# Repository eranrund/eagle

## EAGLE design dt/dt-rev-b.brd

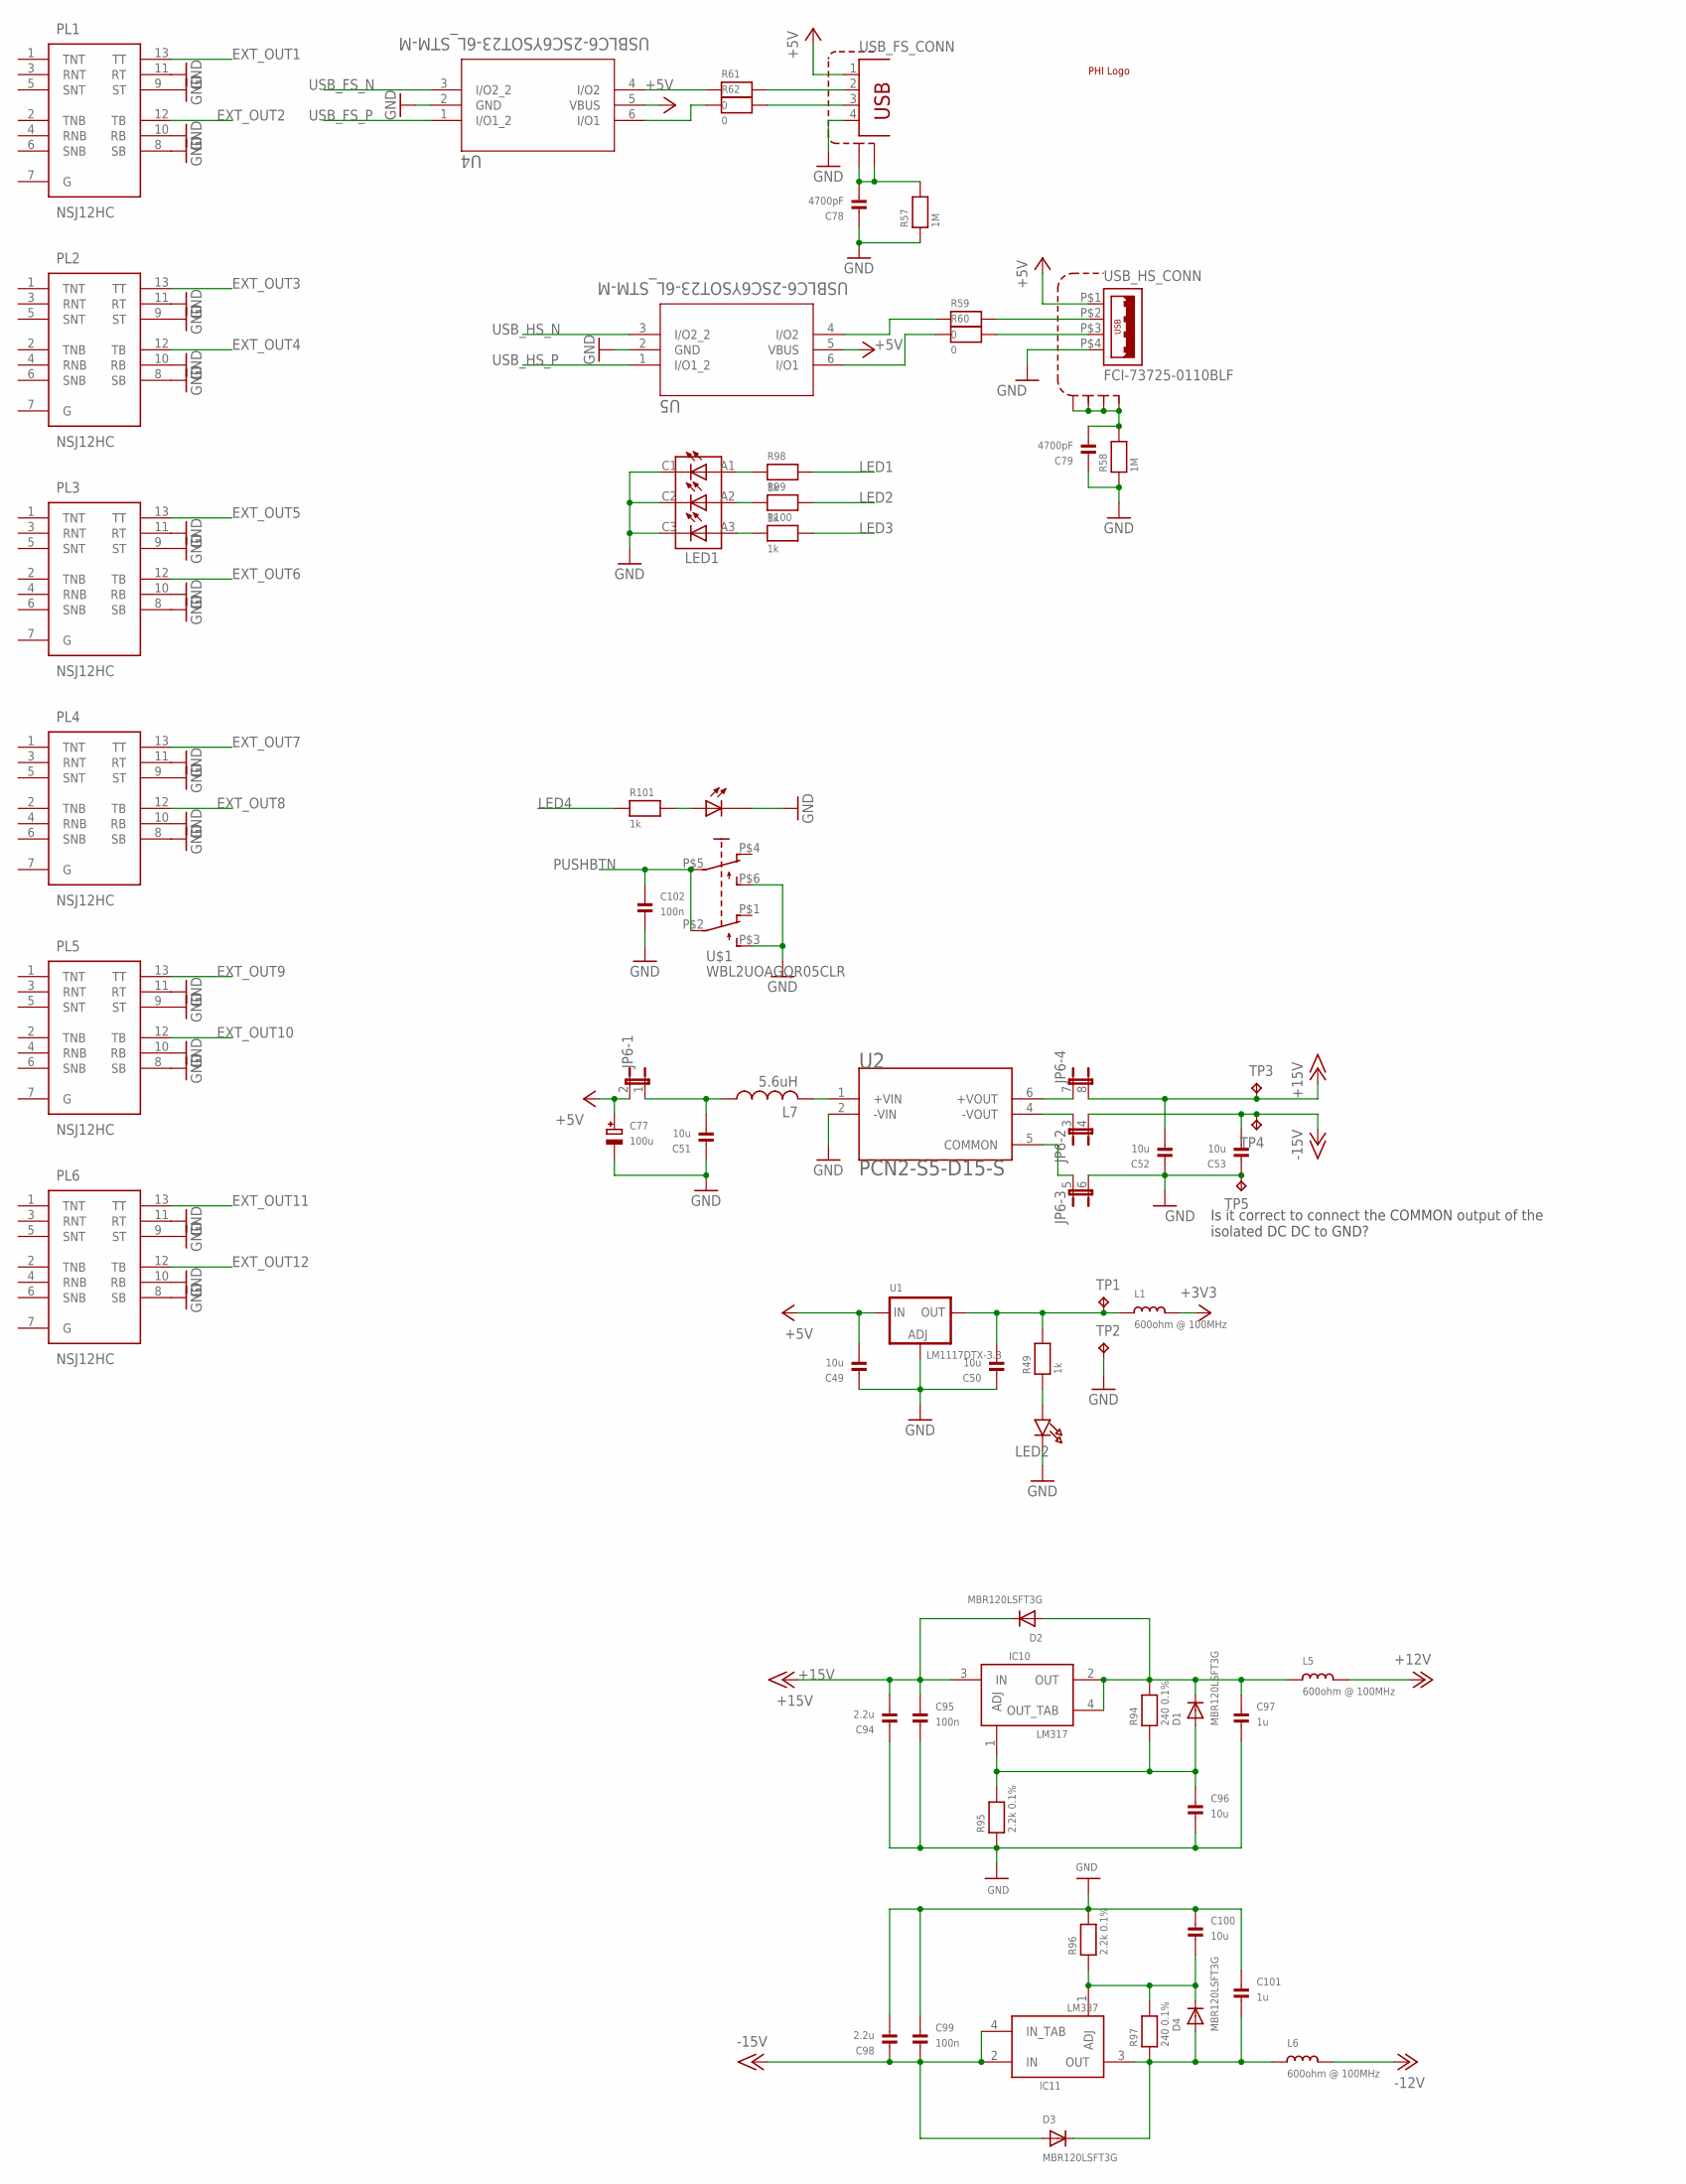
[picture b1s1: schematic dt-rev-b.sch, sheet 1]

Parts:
C49, C50, C51, C52, C53, C96, C100: 10u; 0805; PARTNO CL21A106KAYNNNE
C77: 100u; PANASONIC_D; PARTNO EEE-HAV101XAP
C78, C79: 4700pF; 0603; PARTNO GRM1885C1H472JA01D
C94, C98: 2.2u; 0805; PARTNO UMK212BB7225KG-T
C95, C99, C102: 100n; 0603; PARTNO CC0603KRX7R9BB104
C97, C101: 1u; 1206; PARTNO 12065C105M4Z2A
D1, D2, D3, D4: MBR120LSFT3G; SOD-123; PARTNO MBR120LSFT3G
IC10: LM317; SOT223; PARTNO LM317MBSTT3G
IC11: LM337; SOT223; PARTNO LM337IMPX/NOPB
JP6: JP4QE; JP4Q; PARTNO M20-9760446
L1, L5, L6: 600ohm @ 100MHz; 0603; PARTNO BLM18KG601SN1D
L7: 5.6uH; L1812; PARTNO PM1812-5R6J-RC
LED1: WP934SA_LILYLGDLED; WP934SALILYLGD; PARTNO WP934SA/LILYLGD
LED2: LED0805; CHIPLED_0805; PARTNO AP2012HD
PL1, PL2, PL3, PL4, PL5, PL6: NSJ12HC; NSJ12HF1; PARTNO NSJ12HC
R49, R98, R99, R100, R101: 1k; 0603; PARTNO CRCW06031K00FKEAC
R57, R58: 1M; 0603; PARTNO AC0603FR-131ML
R59, R60, R61, R62: 0; 0603; PARTNO CRCW06030000Z0EBC
R94, R97: 240 0.1%; 0603; PARTNO ERA-3AEB241V
R95, R96: 2.2k 0.1%; 0603; PARTNO ERA-3VEB2201V
TP1, TP2, TP3, TP4, TP5: TPPAD1-13; P1-13; PARTNO 5001
U1: LM1117DTX-3.3; TO252; PARTNO LM1117DTX-3.3/NOPB
U2: PCN2-S5-D15-S; CONV_PCN2-S5-D12-S; PARTNO PCN2-S5-D15-S
U4, U5: USBLC6-2SC6YSOT23-6L_STM-M; SOT23-6L_STM-M; PARTNO USBLC6-2SC6Y
U$1: WBL2UOAGQR05CLR; WBL2UOAGQ; PARTNO WBL2UOAGQR05CLR
U$2: PHI-LOGO
USB_FS: TE-292304-1; PARTNO 292304-1
USB_HS: FCI-73725-0110BLF; PARTNO 73725-0110BLF

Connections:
+3V3: L1.2; also elsewhere on the board
+5V: C49.2, C77.+, JP6.2, U1.2 (IN), U4.5 (VBUS), U5.5 (VBUS), USB_FS.1, USB_HS.P$1 (1); also elsewhere on the board
+12V: L5.2; also elsewhere on the board
+15V: C52.2, C94.2, C95.1, D2.C, IC10.3 (IN), JP6.8 (2), TP3.TP
-12V: L6.2; also elsewhere on the board
-15V: C53.2, C98.1, C99.2, D3.A, IC11.2 (IN), IC11.4 (IN_TAB), JP6.4 (2), TP4.TP
EXT_OUT1: PL1.13 (TT); also elsewhere on the board
EXT_OUT2: PL1.12 (TB); also elsewhere on the board
EXT_OUT3: PL2.13 (TT); also elsewhere on the board
EXT_OUT4: PL2.12 (TB); also elsewhere on the board
EXT_OUT5: PL3.13 (TT); also elsewhere on the board
EXT_OUT6: PL3.12 (TB); also elsewhere on the board
EXT_OUT7: PL4.13 (TT); also elsewhere on the board
EXT_OUT8: PL4.12 (TB); also elsewhere on the board
EXT_OUT9: PL5.13 (TT); also elsewhere on the board
EXT_OUT10: PL5.12 (TB); also elsewhere on the board
EXT_OUT11: PL6.13 (TT); also elsewhere on the board
EXT_OUT12: PL6.12 (TB); also elsewhere on the board
GND: C49.1, C50.1, C51.1, C52.1, C53.1, C77.-, C78.1, C79.1, C94.1, C95.2, C96.2, C97.2, C98.2, C99.1, C100.1, C101.1, C102.2, JP6.6 (2), LED1.C1 (K_1), LED1.C2 (K_2), LED1.C3 (K_3), LED2.C, PL1.8 (SB), PL1.9 (ST), PL1.10 (RB), PL1.11 (RT), PL2.8 (SB), PL2.9 (ST), PL2.10 (RB), PL2.11 (RT), PL3.8 (SB), PL3.9 (ST), PL3.10 (RB), PL3.11 (RT), PL4.8 (SB), PL4.9 (ST), PL4.10 (RB), PL4.11 (RT), PL5.8 (SB), PL5.9 (ST), PL5.10 (RB), PL5.11 (RT), PL6.8 (SB), PL6.9 (ST), PL6.10 (RB), PL6.11 (RT), R57.1, R58.1, R95.1, R96.2, TP2.TP, TP5.TP, U1.1 (ADJ), U2.2 (-VIN), U4.2 (GND), U5.2 (GND), U$1.LED-, U$1.P$3 (OUT1_NO), U$1.P$6 (OUT2_NO), USB_FS.4, USB_HS.P$4 (4); also elsewhere on the board
LED1: R98.2; also elsewhere on the board
LED2: R99.2; also elsewhere on the board
LED3: R100.2; also elsewhere on the board
LED4: R101.1; also elsewhere on the board
unnamed: LED2.A, R49.1
unnamed: C50.2, L1.1, R49.2, TP1.TP, U1.3 (OUT)
unnamed: L7.2, U2.1 (+VIN)
unnamed: JP6.5 (1), U2.5 (COMMON)
unnamed: JP6.7 (1), U2.6 (+VOUT)
unnamed: JP6.3 (1), U2.4 (-VOUT)
unnamed: C51.2, JP6.1, L7.1
unnamed: C78.2, R57.2, USB_FS.P$1 (S1), USB_FS.P$2 (S2)
unnamed: C79.2, R58.2, USB_HS.M1 (S1), USB_HS.M2 (S2), USB_HS.M3 (S3), USB_HS.M4 (S4)
unnamed: C97.1, D1.C, D2.A, IC10.2 (OUT), IC10.4 (OUT_TAB), L5.1, R94.2
unnamed: C96.1, D1.A, IC10.1 (ADJ), R94.1, R95.2
unnamed: C101.2, D3.C, D4.A, IC11.3 (OUT), L6.1, R97.1
unnamed: C100.2, D4.C, IC11.1 (ADJ), R96.1, R97.2
unnamed: LED1.A2 (A_2), R99.1
unnamed: LED1.A3 (A_3), R100.1
unnamed: LED1.A1 (A_1), R98.1
unnamed: R101.2, U$1.LED+
PUSHBTN: C102.1, U$1.P$2 (IN1), U$1.P$5 (IN2); also elsewhere on the board
USB_DEV_CONN_N: R61.2, USB_FS.2
USB_DEV_CONN_P: R62.2, USB_FS.3
USB_DEV_N: R61.1, U4.4 (I/O2)
USB_DEV_P: R62.1, U4.6 (I/O1)
USB_FS_N: U4.3 (I/O2_2); also elsewhere on the board
USB_FS_P: U4.1 (I/O1_2); also elsewhere on the board
USB_HOST_CONN_N: R59.2, USB_HS.P$2 (2)
USB_HOST_CONN_P: R60.2, USB_HS.P$3 (3)
USB_HOST_N: R59.1, U5.4 (I/O2)
USB_HOST_P: R60.1, U5.6 (I/O1)
USB_HS_N: U5.3 (I/O2_2); also elsewhere on the board
USB_HS_P: U5.1 (I/O1_2); also elsewhere on the board

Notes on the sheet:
Is it correct to connect the COMMON output of the isolated DC DC to GND?

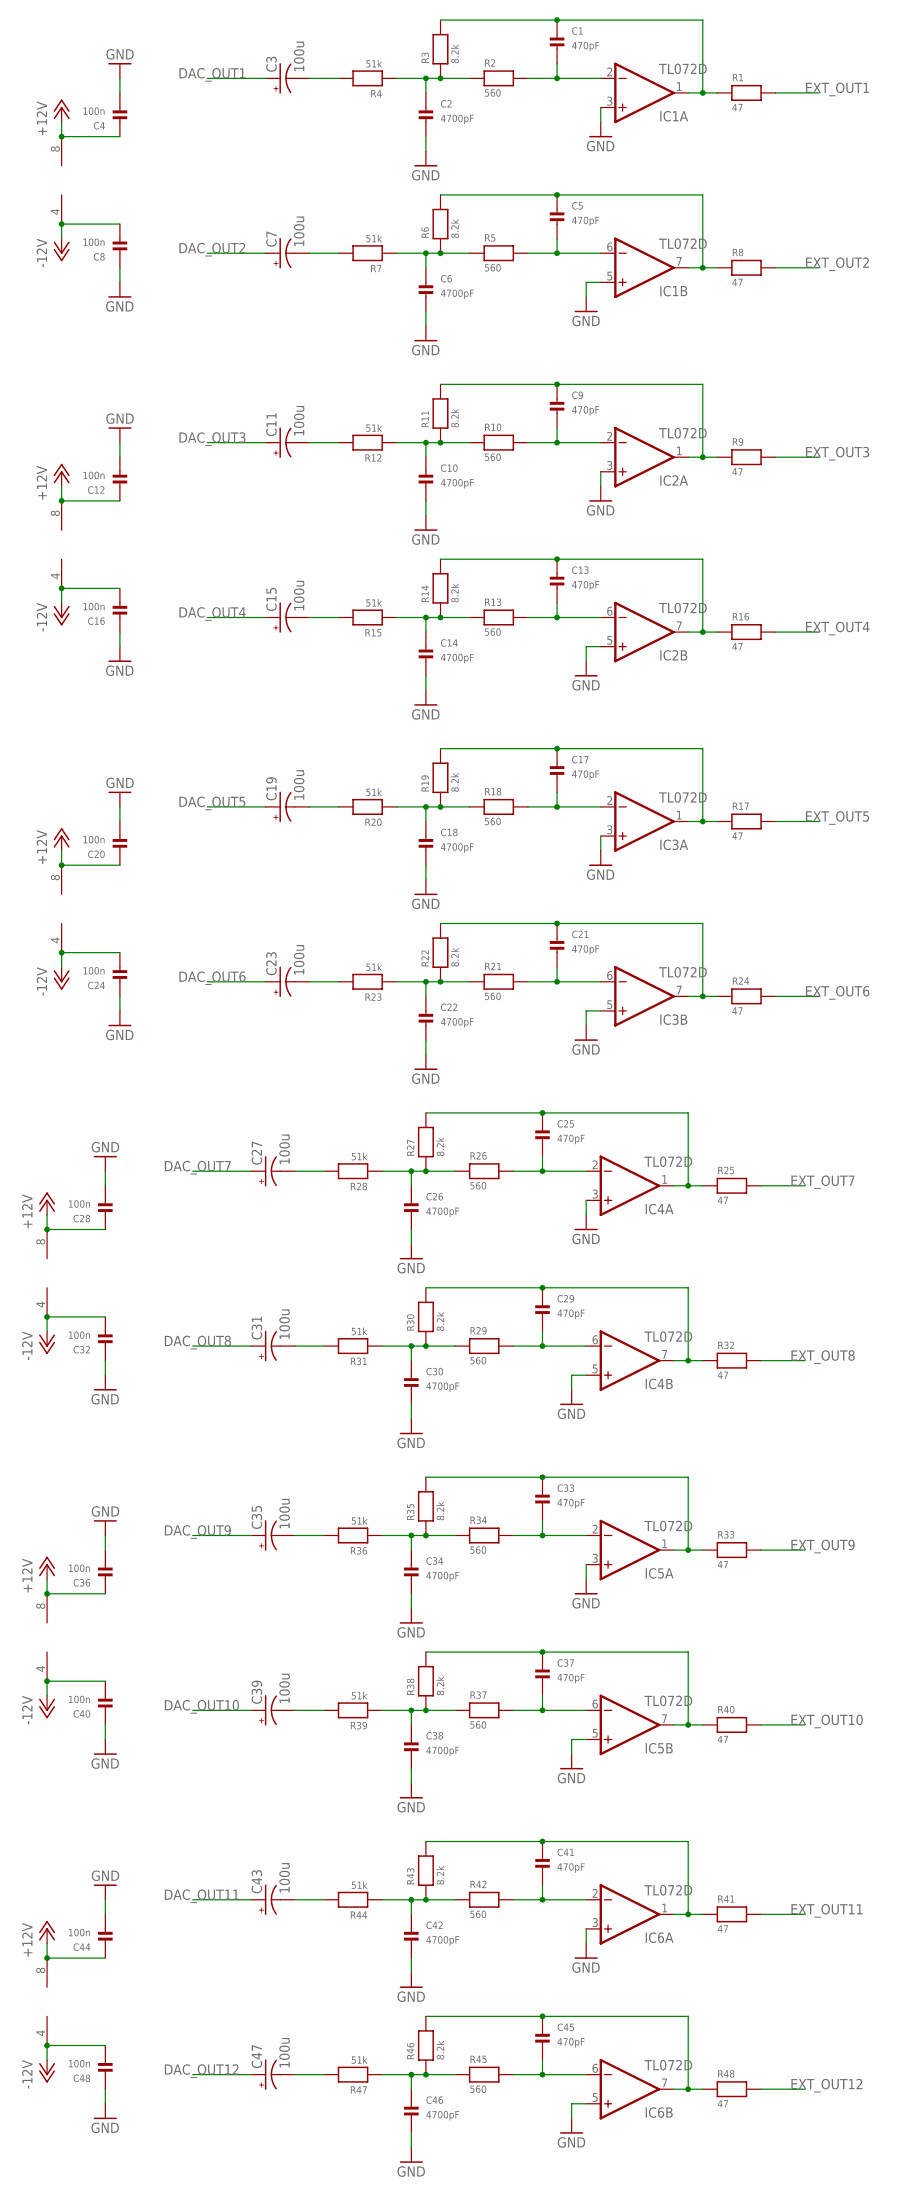
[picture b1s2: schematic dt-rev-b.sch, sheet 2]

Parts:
C1, C5, C9, C13, C17, C21, C25, C29, C33, C37, C41, C45: 470pF; 0603; PARTNO C0603C471J5GACTU
C2, C6, C10, C14, C18, C22, C26, C30, C34, C38, C42, C46: 4700pF; 0603; PARTNO GRM1885C1H472JA01D
C3, C7, C11, C15, C19, C23, C27, C31, C35, C39, C43, C47: 100u; E2-5; PARTNO ESK107M025AC3AA
C4, C8, C12, C16, C20, C24, C28, C32, C36, C40, C44, C48: 100n; 0603; PARTNO CC0603KRX7R9BB104
IC1, IC2, IC3, IC4, IC5, IC6: TL072D; SO08; PARTNO TL072SG-13
R1, R8, R9, R16, R17, R24, R25, R32, R33, R40, R41, R48: 47; 0603; PARTNO CRCW060347R0FKEAC
R2, R5, R10, R13, R18, R21, R26, R29, R34, R37, R42, R45: 560; 0603; PARTNO RC0603FR-07560RL
R3, R6, R11, R14, R19, R22, R27, R30, R35, R38, R43, R46: 8.2k; 0603; PARTNO ERJ-3EKF8201V
R4, R7, R12, R15, R20, R23, R28, R31, R36, R39, R44, R47: 51k; 0603; PARTNO RC0603FR-0751KL

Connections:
+12V: C4.1, C12.1, C20.1, C28.1, C36.1, C44.1, IC1.8 (V+), IC2.8 (V+), IC3.8 (V+), IC4.8 (V+), IC5.8 (V+), IC6.8 (V+); also elsewhere on the board
-12V: C8.2, C16.2, C24.2, C32.2, C40.2, C48.2, IC1.4 (V-), IC2.4 (V-), IC3.4 (V-), IC4.4 (V-), IC5.4 (V-), IC6.4 (V-); also elsewhere on the board
DAC_OUT1: C3.+; also elsewhere on the board
DAC_OUT2: C7.+; also elsewhere on the board
DAC_OUT3: C11.+; also elsewhere on the board
DAC_OUT4: C15.+; also elsewhere on the board
DAC_OUT5: C19.+; also elsewhere on the board
DAC_OUT6: C23.+; also elsewhere on the board
DAC_OUT7: C27.+; also elsewhere on the board
DAC_OUT8: C31.+; also elsewhere on the board
DAC_OUT9: C35.+; also elsewhere on the board
DAC_OUT10: C39.+; also elsewhere on the board
DAC_OUT11: C43.+; also elsewhere on the board
DAC_OUT12: C47.+; also elsewhere on the board
EXT_OUT1: R1.2; also elsewhere on the board
EXT_OUT2: R8.2; also elsewhere on the board
EXT_OUT3: R9.2; also elsewhere on the board
EXT_OUT4: R16.2; also elsewhere on the board
EXT_OUT5: R17.2; also elsewhere on the board
EXT_OUT6: R24.2; also elsewhere on the board
EXT_OUT7: R25.2; also elsewhere on the board
EXT_OUT8: R32.2; also elsewhere on the board
EXT_OUT9: R33.2; also elsewhere on the board
EXT_OUT10: R40.2; also elsewhere on the board
EXT_OUT11: R41.2; also elsewhere on the board
EXT_OUT12: R48.2; also elsewhere on the board
GND: C2.2, C4.2, C6.2, C8.1, C10.2, C12.2, C14.2, C16.1, C18.2, C20.2, C22.2, C24.1, C26.2, C28.2, C30.2, C32.1, C34.2, C36.2, C38.2, C40.1, C42.2, C44.2, C46.2, C48.1, IC1.3 (+IN), IC1.5 (+IN), IC2.3 (+IN), IC2.5 (+IN), IC3.3 (+IN), IC3.5 (+IN), IC4.3 (+IN), IC4.5 (+IN), IC5.3 (+IN), IC5.5 (+IN), IC6.3 (+IN), IC6.5 (+IN); also elsewhere on the board
unnamed: C1.2, IC1.2 (-IN), R2.2
unnamed: C1.1, IC1.1 (OUT), R1.1, R3.2
unnamed: C2.1, R2.1, R3.1, R4.1
unnamed: C3.-, R4.2
unnamed: C5.2, IC1.6 (-IN), R5.2
unnamed: C5.1, IC1.7 (OUT), R6.2, R8.1
unnamed: C6.1, R5.1, R6.1, R7.1
unnamed: C7.-, R7.2
unnamed: C9.2, IC2.2 (-IN), R10.2
unnamed: C9.1, IC2.1 (OUT), R9.1, R11.2
unnamed: C10.1, R10.1, R11.1, R12.1
unnamed: C11.-, R12.2
unnamed: C13.2, IC2.6 (-IN), R13.2
unnamed: C13.1, IC2.7 (OUT), R14.2, R16.1
unnamed: C14.1, R13.1, R14.1, R15.1
unnamed: C15.-, R15.2
unnamed: C17.2, IC3.2 (-IN), R18.2
unnamed: C17.1, IC3.1 (OUT), R17.1, R19.2
unnamed: C18.1, R18.1, R19.1, R20.1
unnamed: C19.-, R20.2
unnamed: C21.2, IC3.6 (-IN), R21.2
unnamed: C21.1, IC3.7 (OUT), R22.2, R24.1
unnamed: C22.1, R21.1, R22.1, R23.1
unnamed: C23.-, R23.2
unnamed: C25.2, IC4.2 (-IN), R26.2
unnamed: C25.1, IC4.1 (OUT), R25.1, R27.2
unnamed: C26.1, R26.1, R27.1, R28.1
unnamed: C27.-, R28.2
unnamed: C29.2, IC4.6 (-IN), R29.2
unnamed: C29.1, IC4.7 (OUT), R30.2, R32.1
unnamed: C30.1, R29.1, R30.1, R31.1
unnamed: C31.-, R31.2
unnamed: C33.2, IC5.2 (-IN), R34.2
unnamed: C33.1, IC5.1 (OUT), R33.1, R35.2
unnamed: C34.1, R34.1, R35.1, R36.1
unnamed: C35.-, R36.2
unnamed: C37.2, IC5.6 (-IN), R37.2
unnamed: C37.1, IC5.7 (OUT), R38.2, R40.1
unnamed: C38.1, R37.1, R38.1, R39.1
unnamed: C39.-, R39.2
unnamed: C41.2, IC6.2 (-IN), R42.2
unnamed: C41.1, IC6.1 (OUT), R41.1, R43.2
unnamed: C42.1, R42.1, R43.1, R44.1
unnamed: C43.-, R44.2
unnamed: C45.2, IC6.6 (-IN), R45.2
unnamed: C45.1, IC6.7 (OUT), R46.2, R48.1
unnamed: C46.1, R45.1, R46.1, R47.1
unnamed: C47.-, R47.2

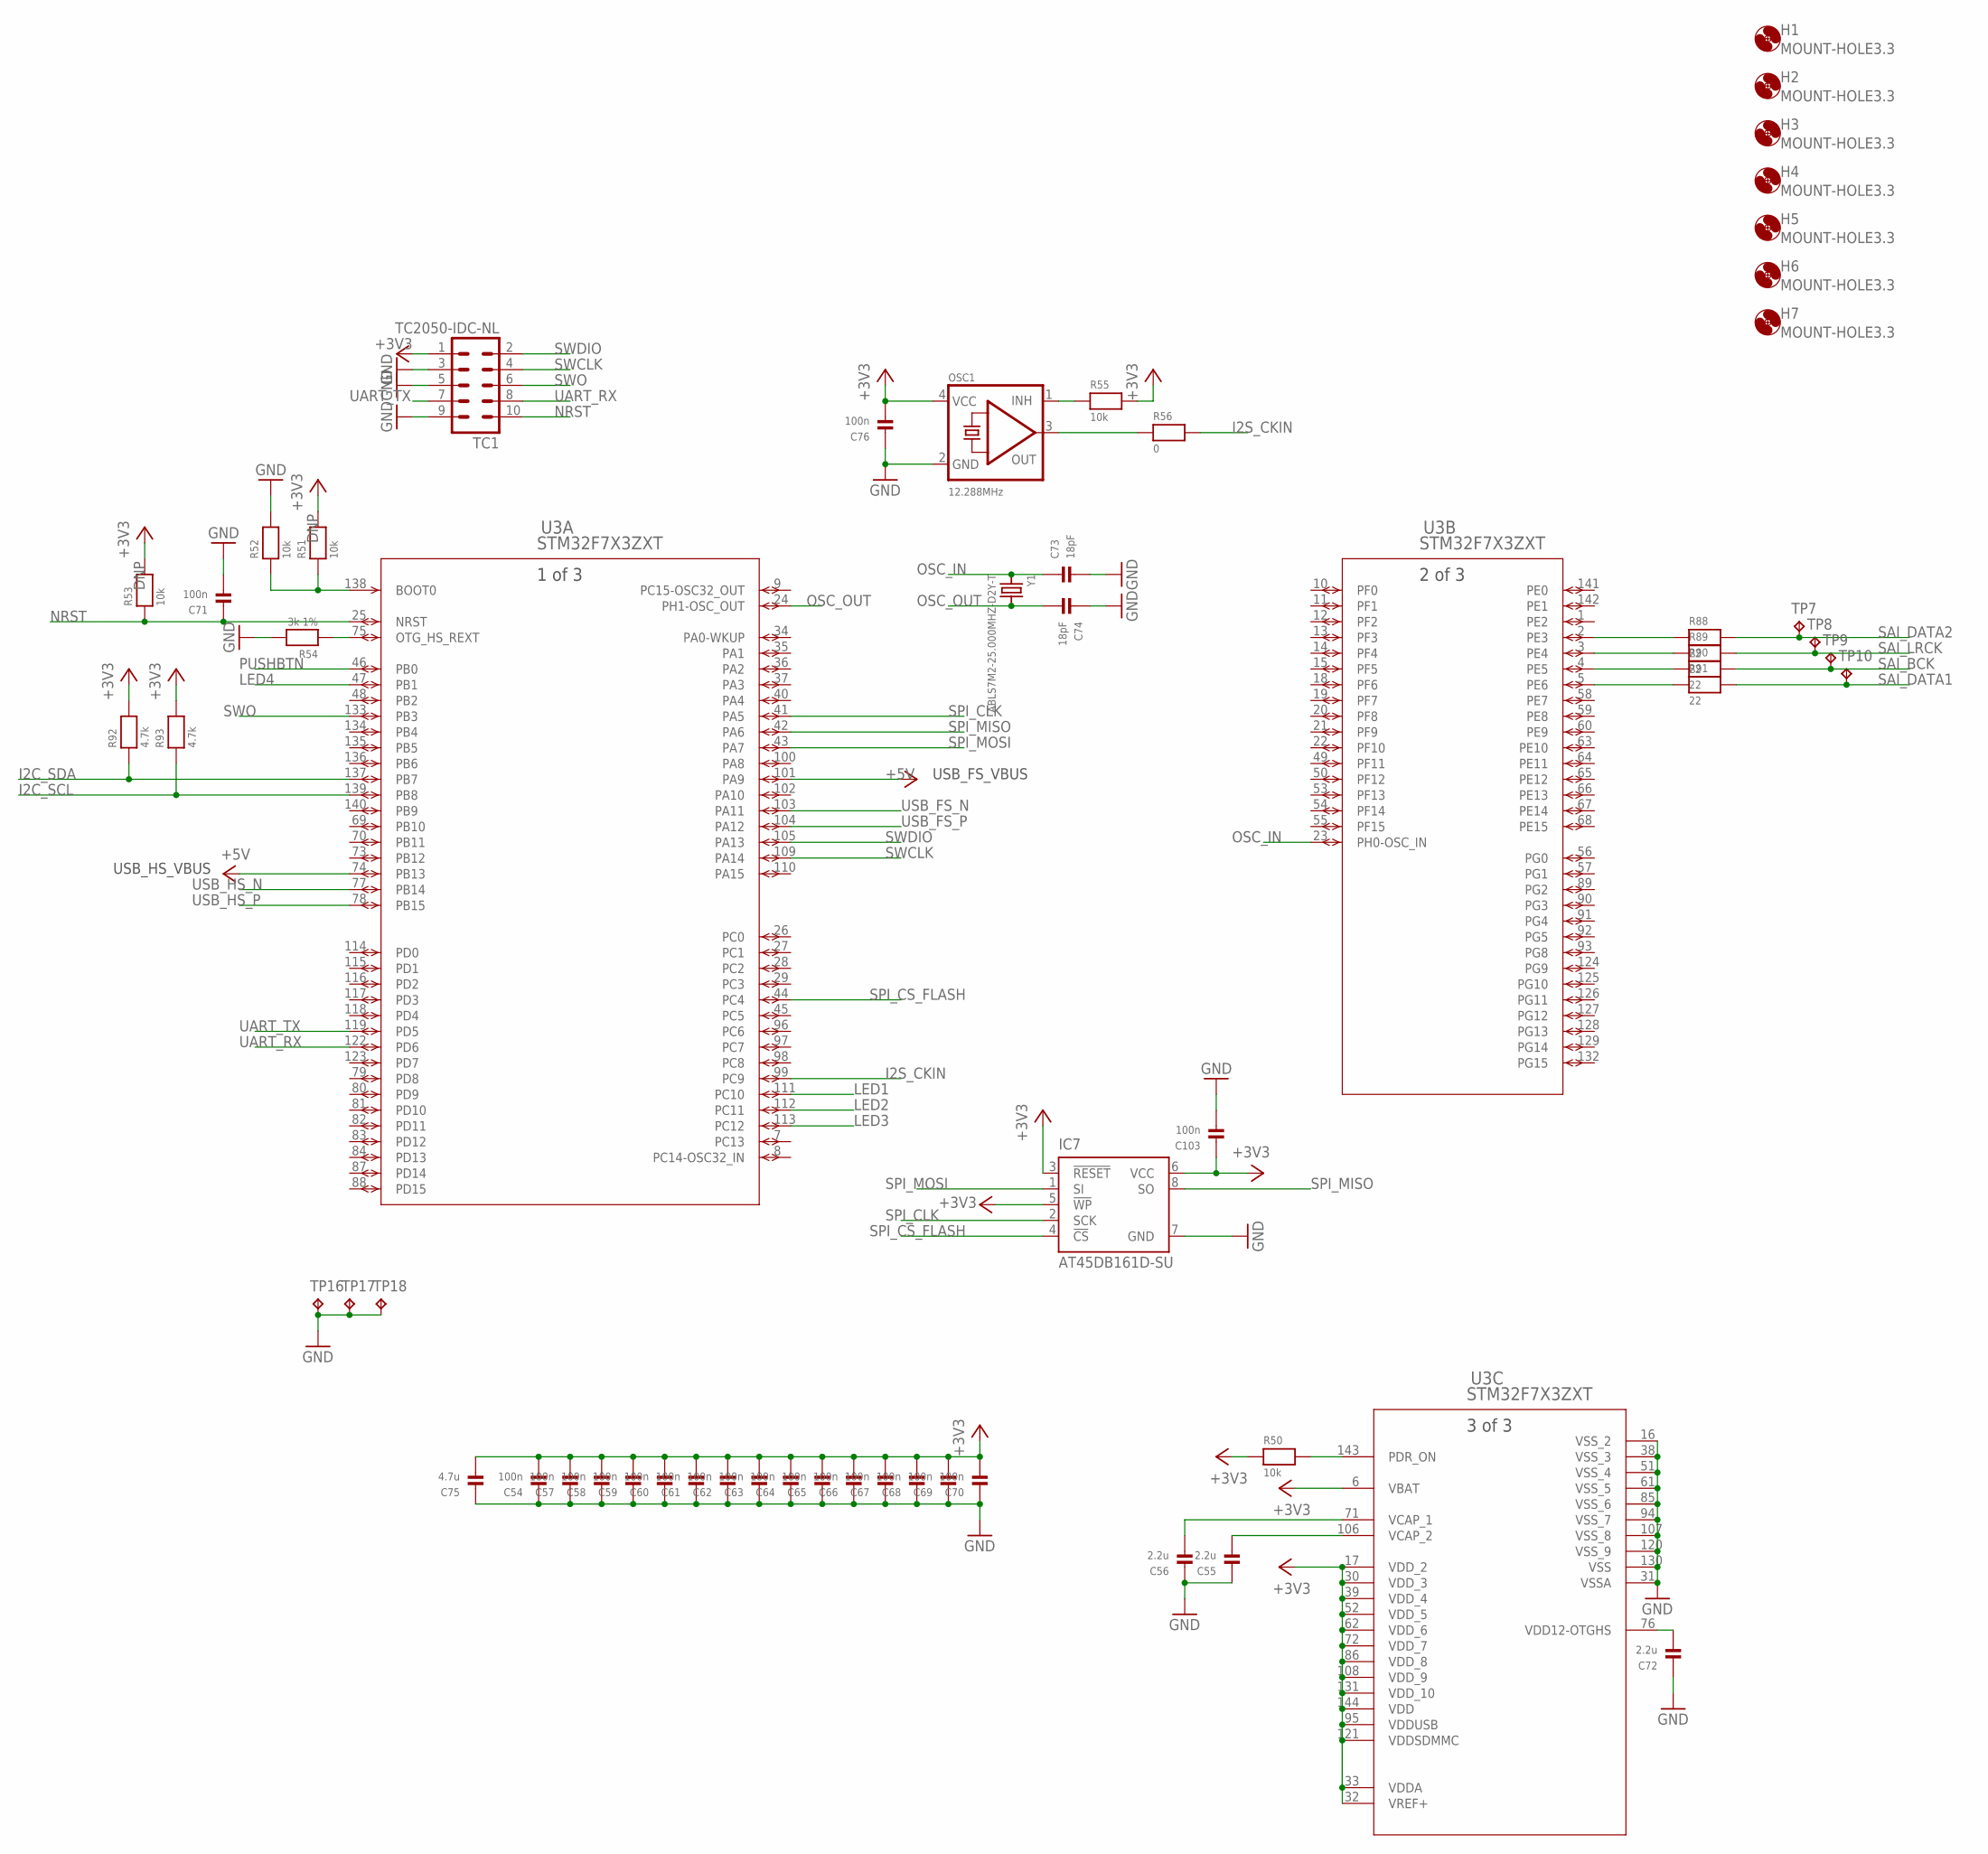
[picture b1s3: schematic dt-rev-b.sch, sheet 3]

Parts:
C54, C57, C58, C59, C60, C61, C62, C63, C64, C65, C66, C67, C68, C69, C70, C71, C76, C103: 100n; 0603; PARTNO CC0603KRX7R9BB104
C55, C56, C72: 2.2u; 1206; PARTNO CL31B225KBHNNNE
C73, C74: 18pF; 0603; PARTNO 06035A180JAT2A
C75: 4.7u; 0603; PARTNO GRM188Z71A475ME15D
H1, H2, H3, H4, H5, H6, H7: MOUNT-HOLE3.3; 3,3; PARTNO *
IC7: AT45DB161D-SU; SOIC8; PARTNO AT45DB161D-SU
OSC1: 12.288MHz; OSC_7X5MM; PARTNO C3391-12.288
R50, R51, R52, R53, R55: 10k; 0603; PARTNO CRCW060310K0JNEBC
R54: 3k 1%; 0603; PARTNO AF0603FR-073KL
R56: 0; 0603; PARTNO CRCW06030000Z0EBC
R88, R89, R90, R91: 22; 0603; PARTNO CRCW060322R0FKEAC
R92, R93: 4.7k; 0603; PARTNO CRCW06034K70FKEA
TC1: TC2050-IDC-NL
TP7, TP8, TP9, TP10, TP16, TP17, TP18: TPPAD1-13; P1-13; PARTNO 5001
U3: STM32F7X3ZXT; LQFP144-20X20MM; PARTNO STM32F733ZET6
Y1: ABLS7M2-25.000MHZ-D2Y-T; ABLS7M225000MHZD2YT; PARTNO ABLS7M2-25.000MHZ-D2Y-T

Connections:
+3V3: C54.2, C57.2, C58.2, C59.2, C60.2, C61.2, C62.2, C63.2, C64.2, C65.2, C66.2, C67.2, C68.2, C69.2, C70.2, C75.2, C76.2, C103.1, IC7.3 (!RESET), IC7.5 (!WP), IC7.6 (VCC), OSC1.4 (VCC), R50.1, R51.2, R53.2, R55.2, R92.2, R93.2, TC1.1, U3.6 (VBAT), U3.17 (VDD_2), U3.30 (VDD_3), U3.32 (VREF+), U3.33 (VDDA), U3.39 (VDD_4), U3.52 (VDD_5), U3.62 (VDD_6), U3.72 (VDD_7), U3.86 (VDD_8), U3.95 (VDDUSB), U3.108 (VDD_9), U3.121 (VDDSDMMC), U3.131 (VDD_10), U3.144 (VDD); also elsewhere on the board
+5V: U3.74 (PB13), U3.101 (PA9); also elsewhere on the board
GND: C54.1, C55.1, C56.1, C57.1, C58.1, C59.1, C60.1, C61.1, C62.1, C63.1, C64.1, C65.1, C66.1, C67.1, C68.1, C69.1, C70.1, C71.2, C72.1, C73.2, C74.1, C75.1, C76.1, C103.2, IC7.7 (GND), OSC1.2 (GND), R52.2, R54.2, TC1.3, TC1.5, TC1.9, TP16.TP, TP17.TP, TP18.TP, U3.16 (VSS_2), U3.31 (VSSA), U3.38 (VSS_3), U3.51 (VSS_4), U3.61 (VSS_5), U3.85 (VSS_6), U3.94 (VSS_7), U3.107 (VSS_8), U3.120 (VSS_9), U3.130 (VSS); also elsewhere on the board
I2C_SCL: R93.1, U3.139 (PB8); also elsewhere on the board
I2C_SDA: R92.1, U3.137 (PB7); also elsewhere on the board
I2S_CKIN: R56.2, U3.99 (PC9)
LED1: U3.111 (PC10); also elsewhere on the board
LED2: U3.112 (PC11); also elsewhere on the board
LED3: U3.113 (PC12); also elsewhere on the board
LED4: U3.47 (PB1); also elsewhere on the board
unnamed: C56.2, U3.71 (VCAP_1)
unnamed: C55.2, U3.106 (VCAP_2)
unnamed: R50.2, U3.143 (PDR_ON)
unnamed: R51.1, R52.1, U3.138 (BOOT0)
unnamed: R54.1, U3.75 (OTG_HS_REXT)
unnamed: C72.2, U3.76 (VDD12-OTGHS)
unnamed: OSC1.1 (INH), R55.1
unnamed: OSC1.3 (OUT), R56.1
unnamed: R88.1, U3.2 (PE3)
unnamed: R89.1, U3.3 (PE4)
unnamed: R90.1, U3.4 (PE5)
unnamed: R91.1, U3.5 (PE6)
NRST: C71.1, R53.1, TC1.10, U3.25 (NRST)
OSC_IN: C73.1, U3.23 (PH0-OSC_IN), Y1.1
OSC_OUT: C74.2, U3.24 (PH1-OSC_OUT), Y1.2
PUSHBTN: U3.46 (PB0); also elsewhere on the board
SAI_BCK: R90.2, TP9.TP; also elsewhere on the board
SAI_DATA1: R91.2, TP10.TP; also elsewhere on the board
SAI_DATA2: R88.2, TP7.TP; also elsewhere on the board
SAI_LRCK: R89.2, TP8.TP; also elsewhere on the board
SPI_CLK: IC7.2 (SCK), U3.41 (PA5)
SPI_CS_FLASH: IC7.4 (!CS), U3.44 (PC4)
SPI_MISO: IC7.8 (SO), U3.42 (PA6)
SPI_MOSI: IC7.1 (SI), U3.43 (PA7)
SWCLK: TC1.4, U3.109 (PA14)
SWDIO: TC1.2, U3.105 (PA13)
SWO: TC1.6, U3.133 (PB3)
UART_RX: TC1.8, U3.122 (PD6)
UART_TX: TC1.7, U3.119 (PD5)
USB_FS_N: U3.103 (PA11); also elsewhere on the board
USB_FS_P: U3.104 (PA12); also elsewhere on the board
USB_HS_N: U3.77 (PB14); also elsewhere on the board
USB_HS_P: U3.78 (PB15); also elsewhere on the board

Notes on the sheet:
USB_FS_VBUS
USB_HS_VBUS

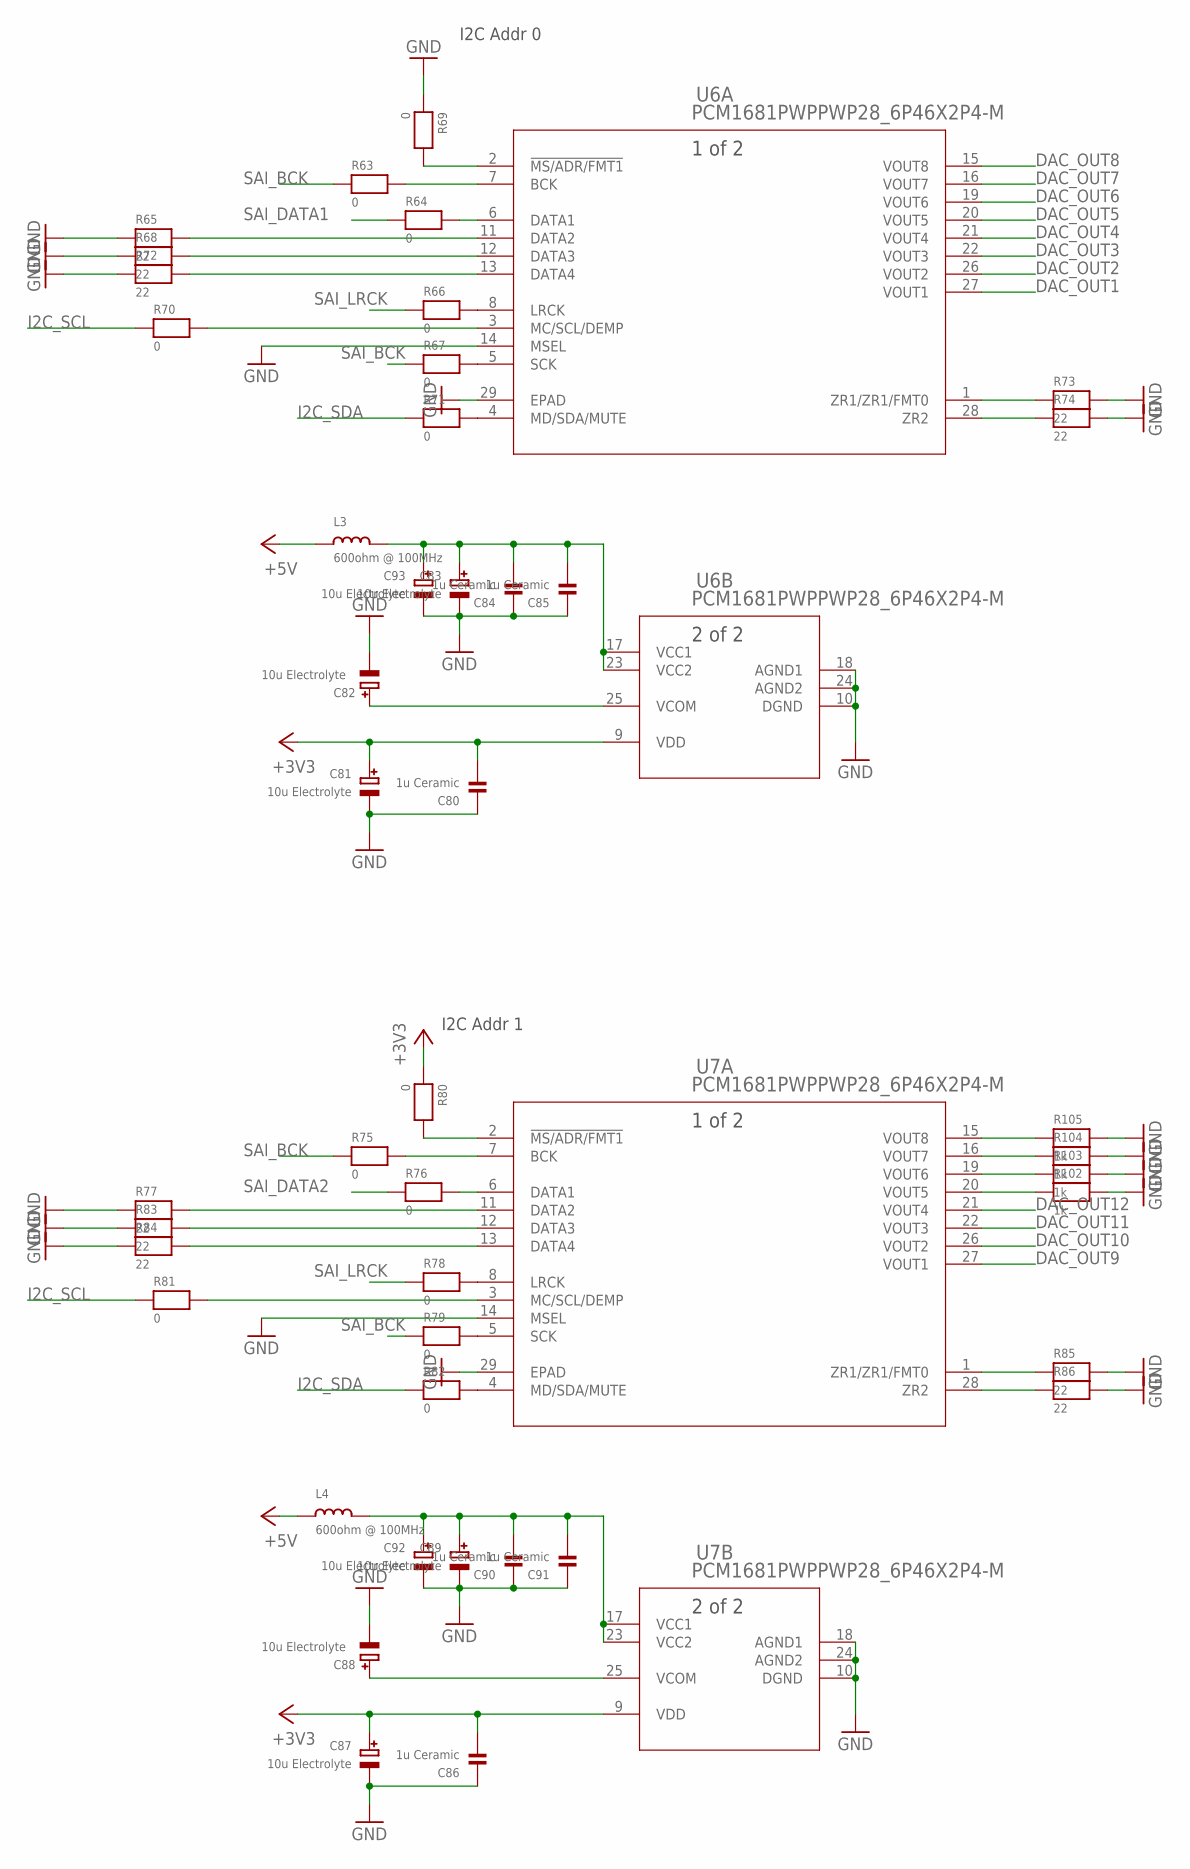
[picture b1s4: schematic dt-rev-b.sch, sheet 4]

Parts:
C80, C84, C85, C86, C90, C91: 1u Ceramic; 0603; PARTNO GMK107AB7105KAHT
C81, C82, C83, C87, C88, C89, C92, C93: 10u Electrolyte; PANASONIC_C; PARTNO EEE-HA1V100R
L3, L4: 600ohm @ 100MHz; 0603; PARTNO BLM18KG601SN1D
R63, R64, R66, R67, R69, R70, R71, R75, R76, R78, R79, R80, R81, R82: 0; 0603; PARTNO CRCW06030000Z0EBC
R65, R68, R72, R73, R74, R77, R83, R84, R85, R86: 22; 0603; PARTNO CRCW060322R0FKEAC
R102, R103, R104, R105: 1k; 0603; PARTNO CRCW06031K00FKEAC
U6, U7: PCM1681PWPPWP28_6P46X2P4-M; PWP28_6P46X2P4-M; PARTNO PCM1681PWP

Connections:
+3V3: C80.2, C81.+, C86.2, C87.+, R80.1, U6.9 (VDD), U7.9 (VDD); also elsewhere on the board
+5V: L3.1, L4.1; also elsewhere on the board
DAC_OUT1: U6.27 (VOUT1); also elsewhere on the board
DAC_OUT2: U6.26 (VOUT2); also elsewhere on the board
DAC_OUT3: U6.22 (VOUT3); also elsewhere on the board
DAC_OUT4: U6.21 (VOUT4); also elsewhere on the board
DAC_OUT5: U6.20 (VOUT5); also elsewhere on the board
DAC_OUT6: U6.19 (VOUT6); also elsewhere on the board
DAC_OUT7: U6.16 (VOUT7); also elsewhere on the board
DAC_OUT8: U6.15 (VOUT8); also elsewhere on the board
DAC_OUT9: U7.27 (VOUT1); also elsewhere on the board
DAC_OUT10: U7.26 (VOUT2); also elsewhere on the board
DAC_OUT11: U7.22 (VOUT3); also elsewhere on the board
DAC_OUT12: U7.21 (VOUT4); also elsewhere on the board
GND: C80.1, C81.-, C82.-, C83.-, C84.1, C85.1, C86.1, C87.-, C88.-, C89.-, C90.1, C91.1, C92.-, C93.-, R65.1, R68.1, R69.1, R72.1, R73.2, R74.2, R77.1, R83.1, R84.1, R85.2, R86.2, R102.2, R103.2, R104.2, R105.2, U6.10 (DGND), U6.14 (MSEL), U6.18 (AGND1), U6.24 (AGND2), U6.29 (EPAD), U7.10 (DGND), U7.14 (MSEL), U7.18 (AGND1), U7.24 (AGND2), U7.29 (EPAD); also elsewhere on the board
I2C_SCL: R70.1, R81.1; also elsewhere on the board
I2C_SDA: R71.1, R82.1; also elsewhere on the board
unnamed: R73.1, U6.1 (ZR1/ZR1/FMT0)
unnamed: R74.1, U6.28 (ZR2)
unnamed: R69.2, U6.2 (!MS/ADR/FMT1)
unnamed: C82.+, U6.25 (VCOM)
unnamed: C83.+, C84.2, C85.2, C93.+, L3.2, U6.17 (VCC1), U6.23 (VCC2)
unnamed: R63.2, U6.7 (BCK)
unnamed: R64.2, U6.6 (DATA1)
unnamed: R65.2, U6.11 (DATA2)
unnamed: R66.2, U6.8 (LRCK)
unnamed: R68.2, U6.12 (DATA3)
unnamed: R72.2, U6.13 (DATA4)
unnamed: R67.2, U6.5 (SCK)
unnamed: R70.2, U6.3 (MC/SCL/DEMP)
unnamed: R71.2, U6.4 (MD/SDA/MUTE)
unnamed: R102.1, U7.20 (VOUT5)
unnamed: R103.1, U7.19 (VOUT6)
unnamed: R104.1, U7.16 (VOUT7)
unnamed: R105.1, U7.15 (VOUT8)
unnamed: R85.1, U7.1 (ZR1/ZR1/FMT0)
unnamed: R86.1, U7.28 (ZR2)
unnamed: C88.+, U7.25 (VCOM)
unnamed: C89.+, C90.2, C91.2, C92.+, L4.2, U7.17 (VCC1), U7.23 (VCC2)
unnamed: R75.2, U7.7 (BCK)
unnamed: R76.2, U7.6 (DATA1)
unnamed: R77.2, U7.11 (DATA2)
unnamed: R78.2, U7.8 (LRCK)
unnamed: R79.2, U7.5 (SCK)
unnamed: R80.2, U7.2 (!MS/ADR/FMT1)
unnamed: R81.2, U7.3 (MC/SCL/DEMP)
unnamed: R82.2, U7.4 (MD/SDA/MUTE)
unnamed: R83.2, U7.12 (DATA3)
unnamed: R84.2, U7.13 (DATA4)
SAI_BCK: R63.1, R67.1, R75.1, R79.1; also elsewhere on the board
SAI_DATA1: R64.1; also elsewhere on the board
SAI_DATA2: R76.1; also elsewhere on the board
SAI_LRCK: R66.1, R78.1; also elsewhere on the board

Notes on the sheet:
I2C Addr 0
I2C Addr 1

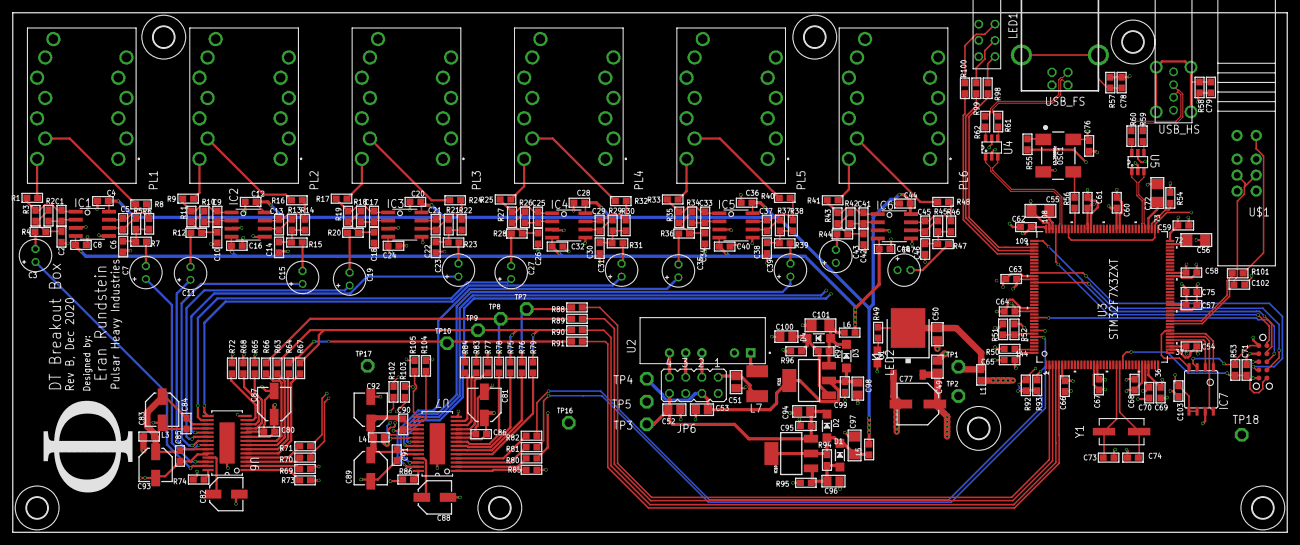
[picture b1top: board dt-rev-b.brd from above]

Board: 4 copper layers, 199.4 x 81.3 mm, 268 parts (0 on the bottom side), 176 nets.

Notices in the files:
parts and their libraries:
microbuilder: This work is placed in the public domain, and may be freely used for commercial and non-commercial work with the following conditions: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
r-78xx_10: (c) 2015 Samuel Lourenço
COPYRIGHT: Copyright (C) 2016 Accelerated Designs. All rights reserved
